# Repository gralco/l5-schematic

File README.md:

# l5-schematic

The Librem 5 schematics and layout files (mainboard, USB-C board, and USB-C FPC flex cable).

The [EDA CAD files](./CAD/) included are the [PADS](./CAD/PADS/) schematic and layout that were used to produce the Librem 5 boards,
as well as [KiCad](./CAD/KiCad/) files which are a converted capture of the PADS design that are in a reliable reference draft state.

## License
[GNU GPLv3+](./LICENSE)

## Mechanical Designs
The Librem 5's mechanical designs can be found in the [Librem5/3D_designs](https://source.puri.sm/Librem5/3D_designs) repo.

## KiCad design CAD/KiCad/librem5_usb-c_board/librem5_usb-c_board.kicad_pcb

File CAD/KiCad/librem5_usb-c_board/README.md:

# Librem 5 USB-C Board KiCad Conversion
Project to convert the Librem 5 USB-C board to KiCad.

## License
GNU GPLv3+

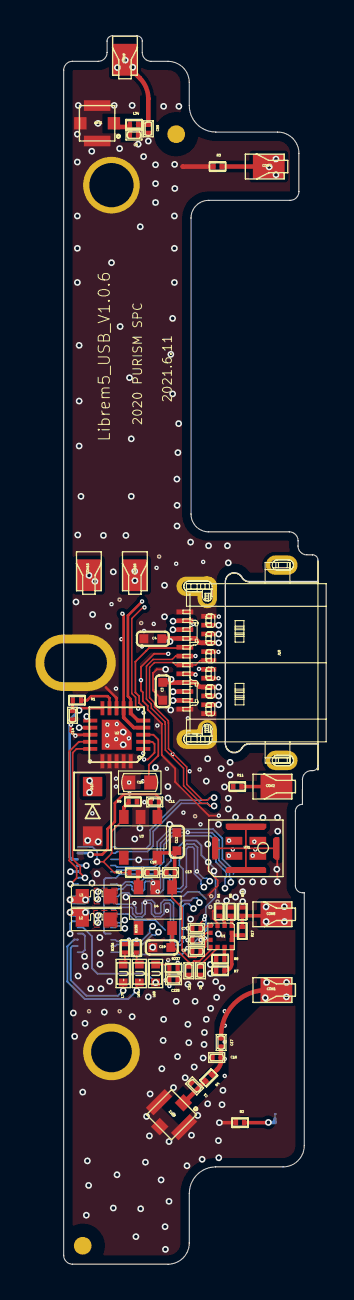
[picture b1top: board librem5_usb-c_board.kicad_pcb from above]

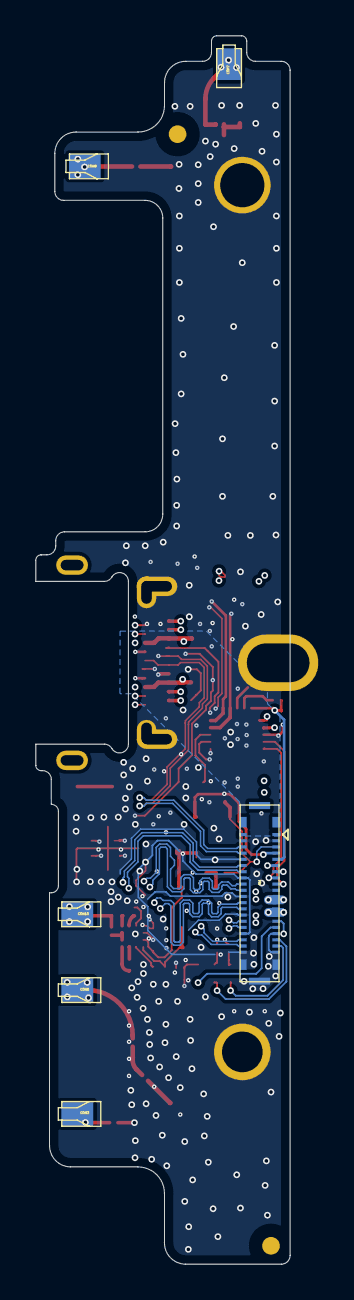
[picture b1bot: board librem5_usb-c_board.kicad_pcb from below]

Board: 6 copper layers, 14.4 x 69.4 mm, 69 parts (6 on the bottom side), 58 nets.

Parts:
ANT1, ANT2: APEX-4
C1, C5, C6, C7, C8, C9, C10, C11, C13, C14, C16, C17, C18, C89, C225: CAP-0201
C3, C4, C12, C19: CAP-0402
C15: CAP-0603
CON1, CON2, CON3, CON4, CON5, CON6, CON7, CON8, CON9, CON10, CON15, CON16: ANT_CON1-CZX
D10: SOD123W
J10: CON-USB-TYPEC-3107A
J11: BTB40-0.35-KYOCERA
L2, L3: IND-0603
L34: RES-0201
L68, L69, L70: IND-0402
R1, R2, R3, R4, R5, R6, R7, R8, R9, R10, R11, R15, R17, R236, R237, R238: RES-0201
TS1, TS3: SC-M1.4F
TS2: PTH_D250_320
TS11: PTH_D230_320
U1: MXD8543E_QFN12
U2: TPD6S300AA
U3, U4: WL2836E_SOT-23-5L
U31: 3SM222FMT1KA
X1: PTH_SLOT_220_355

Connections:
4G_MIPI_SCL: C8.1, J11.34, U1.5
4G_MIPI_SDA: C7.1, J11.35, U1.4
4G_RFSW_EN: J11.3, R9.2, R10.1, U3.3
$$$5995: R5.2, U1.1
$$$6176: R6.2, U1.2
$$$6343: C16.1, C17.2, R4.2
$$$6422: C17.1, CON1.1, CON6.1
$$$7024: R7.1, U1.10
$$$7027: R8.1, U1.9
$$$7350: C6.1, U1.8
$$$10996: CON2.1, R11.2
$$$11668: C18.1, R10.2, U4.3
$$$12116: R1.2, U2.9
$$$12510: R237.2, U31.2
$$$18331: R236.1, U31.4
$$$18332: R238.1, U31.3
$$$19146: C89.1, CON7.1, CON9.1, L34.2
$$$19504: J11.16, L68.1
$$$19505: J11.18, L69.1
$$$19506: J11.19, L70.1
$$$20764: ANT2.1, C1.1, R4.1
$$$23865: C15.1, U2.3
$$$25581: ANT1.1, C5.1, L34.1
$$$32555: R17.1, U1.11, U1.12
ANT_GND: CON5.1, CON10.1, R15.2, R17.2
CC1: J10.A5, U2.4, U2.7
CC1_C: J11.6, U2.12
CC2: J10.B5, U2.5, U2.6
CC2_C: J11.7, U2.11
GND: ANT1.2, ANT1.3, ANT1.4, ANT2.2, ANT2.3, ANT2.4, C1.2, C3.1, C4.1, C5.2, C6.2, C7.2, C8.2, C9.2, C10.2, C11.1, C12.2, C13.1, C14.2, C15.2, C16.2, C18.2, C19.2, C89.2, C225.2, D10.2, J10.A1, J10.A12, J10.B1, J10.B12, J10.SH3, J10.SH4, J10.SH5, J10.SH6, J11.2, J11.10, J11.15, J11.17, J11.20, J11.21, J11.24, J11.27, J11.30, J11.33, J11.36, J11.39, J11.44, J11.45, J11.46, R2.1, R3.1, R5.1, R6.1, R7.2, R8.2, R9.1, R11.1, R15.1, TS2.1, TS11.1, U1.3, U2.8, U2.13, U2.16, U2.17, U2.18, U2.19, U2.20, U2.21, U3.2, U4.2, U31.5, U31.6, U31.7, U31.8, X1.1
MAIN_ANT_GND: CON3.1, R2.2
MIC2_CLK: L69.2, R238.2
MIC2_DAT: L70.2, R236.2
MIC_1V8: C225.1, L68.2, R237.1, U31.1
SBU1: J10.A8, U2.1
SBU1_C: J11.8, U2.15
SBU2_C: J11.9, U2.14
SPKL: CON15.1, L3.2
SPKL_C: J11.11, J11.12, L3.1
SPKR: CON16.1, L2.2
SPKR_C: J11.13, J11.14, L2.1
SSRXN1: J10.B10, J11.31
SSRXN2: J10.A10, J11.22
SSRXP1: J10.B11, J11.32
SSRXP2: J10.A11, J11.23
SSTXN1: J10.A3, J11.28
SSTXN2: J10.B3, J11.25
SSTXP1: J10.A2, J11.29
SSTXP2: J10.B2, J11.26
SUB2: J10.B8, U2.2
USB1_DN_CN: J10.A7, J10.B7, J11.37
USB1_DP_CN: J10.A6, J10.B6, J11.38
USB_PD_LDO3V3: C14.1, J11.5, R1.1, U2.10
VBUS_TYPEC: C3.2, C4.2, D10.1, J10.A4, J10.A9, J10.B4, J10.B9, J11.1, J11.40, J11.41, J11.42, J11.43
VDD28_ANT: C9.1, C12.1, C13.2, U1.6, U3.5, U4.1
VIO18_ANT: C10.1, C19.1, U1.7, U4.5
VSYS_3V4_4V3: C11.2, J11.4, U3.1
WIFI_ANT_GND: CON4.1, CON8.1, R3.2

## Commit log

2019-12-02 Add the v0.9.7 "Birch" schematics
2020-01-07 Add the v0.9.8 "Chestnut" schematics
2020-03-20 Add the SoC pinout spreadsheet
2020-07-08 Add the v1.0.0 "Dogwood" schematics
2020-07-11 Update the pinout spreadsheet to reflect the new GPIO controlling the SHDN pin of the front-facing camera
2020-11-08 Add the v1.0.2 "Evergreen" schematics
2020-11-11 Add TF_NCD to the pinout spreadsheet which is found on pin J22 GPIO3_IO11
2022-02-01 Add the v1.0.3.1 "Evergreen" schematics
2022-02-02 Add the v1.0.6 "Evergreen" schematics
2022-02-02 Add the v1.0.6.1 "Evergreen" schematics
2022-02-02 Add LICENSE
2022-02-21 Add the v1.0.6 "Evergreen" assembly drawings
    These drawings are the same for v1.0.6.1 as well.
2022-12-01 Add the schematic block diagram
    The source file is a LibreOffice draw format. Also included is a PDF.
2023-05-25 Add interactive HTML BOMs for both boards
2023-07-02 Add the latest Librem 5 BOM
    The spreadsheet contains both the main board and usb-c board BOMs as
    separate sheets. Alternative part numbers exist for several parts but
    are not (yet) listed.
2023-07-19 Specify in the notes that the 4GB DRAM and 128GB eMMC is used on the Liberty Phone
2023-08-14 Correct the HKS part number in the BOM
    It should be MK-12C02-G015 instead of MK-12C02-G020 since the length of
    the actuator should be 1.5mm, not 2.0mm.
2023-09-19 Add PDFs of the boards' layers
2024-03-21 Add the USB-C flex cable schematic
2024-03-24 Add an interactive HTML BOM for the USB-C FPC (flex cable board)
2024-03-24 Add the CAD files for the mainboard, USB-C board, and USB-C FPC
2024-03-24 Update READMEs
2024-03-31 .gitignore: Do not track `fp-info-cache` files
2024-06-22 README.md: mention GNU GPLv3+ license
2024-08-18 Add GigaDevices GD25Q16EEIGR as a potential SPI NOR flash for U147
2024-09-23 Add the mainboard's stackup in its KiCad project
2024-09-23 README: Mention the Librem5/3D_designs repo
2024-09-25 Add relative permittivity values for the dielectrics and rename the layers to use KiCad's convention
2024-10-12 KiCad Mainboard: Rename all sheets to correctly follow the sheet numbering
    Update the project to KiCad 8.99
2024-10-12 KiCad Mainboard: Convert all hierarchical labels to global labels since it is a flat schematic
2024-11-09 Set the rev in the title block for each sheet and the layout to v1.0.6.1
2025-01-03 README: fix type "3D_designs"
2025-01-17 README: fix typo "3D_designs"
2025-03-22 BOM: make R48, R66, and R145 become CRCW020110K0FNED (10kOhm 0201)
    This fixes VIH(min) not being reached when the internal pull-ups on the
    HSW_*_STATE SoC pins are disabled, allowing the software to reliably
    detect when the switch is in its on state.
    For now, this is a BOM-only change that has not yet been reflected in
    the schematic.
2026-05-21 Use KiCad's new PADS importer/converter tool to go directly from PADS ascii to KiCad 10, place this newly converted project in CAD/PADS/librem5_mainboard/librem5_mainboard_kicad_conversion/, keep the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
    The one in CAD/KiCad/ seems to be a bit better but this newly converted
    project is available in case it might have some improvements (e.g. in
    cross-probing or some other more accurate details). Either one (or both)
    may be used to completely move the project over to KiCad.
